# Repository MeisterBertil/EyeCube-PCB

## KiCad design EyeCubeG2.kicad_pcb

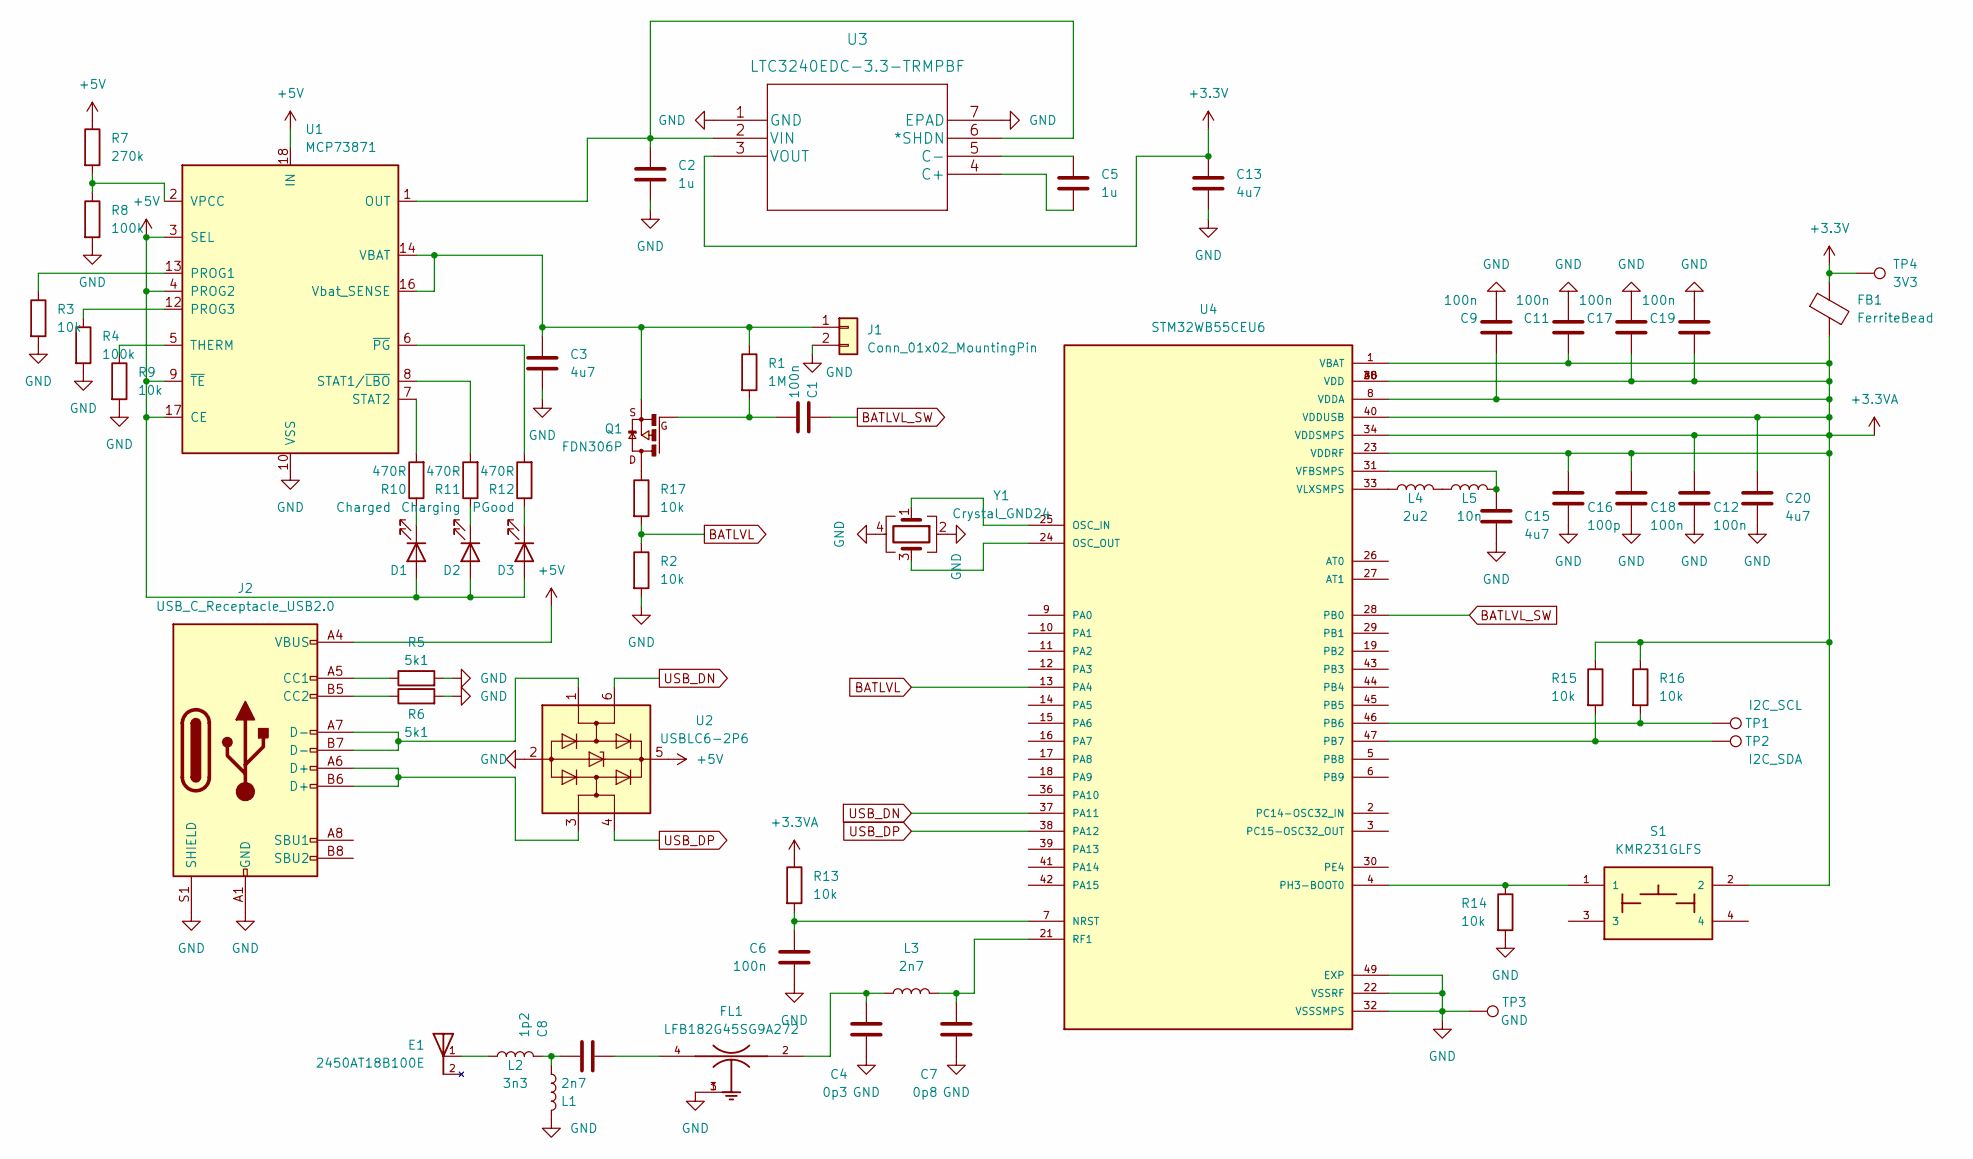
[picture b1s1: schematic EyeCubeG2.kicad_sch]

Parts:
C1, C6, C9, C11, C12, C17, C18, C19: 100n; C_0402_1005Metric
C2, C5: 1u; C_0402_1005Metric
C3, C13, C15, C20: 4u7; C_0603_1608Metric
C4: 0p3; C_0402_1005Metric
C7: 0p8; C_0402_1005Metric
C8: 1p2; C_0402_1005Metric
C16: 100p; C_0402_1005Metric
D1: Charged; D_0402_1005Metric
D2: Charging; D_0402_1005Metric
D3: PGood; D_0402_1005Metric
E1: 2450AT18B100E; XDCR_2450AT18B100E; PARTREV 4.0
FB1: FerriteBead; L_0402_1005Metric
FL1: LFB182G45SG9A272; FIL_LFB182G45SG9A272; PARTREV N/A
J1: Conn_01x02_MountingPin; JST_PH_S2B-PH-K_1x02_P2.00mm_Horizontal
J2: USB_C_Receptacle_USB2.0; USB_C_Receptacle_HRO_TYPE-C-31-M-12
L1, L3: 2n7; L_0402_1005Metric
L2: 3n3; L_0402_1005Metric
L4: 2u2; L_0402_1005Metric
L5: 10n; L_0402_1005Metric
Q1: FDN306P; SSOT-3
R1: 1M; R_0402_1005Metric
R2, R3, R9, R13, R14, R15, R16, R17: 10k; R_0402_1005Metric
R4, R8: 100k; R_0402_1005Metric
R5, R6: 5k1; R_0402_1005Metric
R7: 270k; R_0402_1005Metric
R10, R11, R12: 470R; R_0402_1005Metric
S1: KMR231GLFS; SW4SMD_63X161LS
TP1: I2C_SCL; TestPoint_Pad_D4.0mm
TP2: I2C_SDA; TestPoint_Pad_D4.0mm
TP3: GND; TestPoint_Pad_D4.0mm
TP4: 3V3; TestPoint_Pad_D4.0mm
U1: MCP73871; QFN-20-1EP_4x4mm_P0.5mm_EP2.5x2.5mm
U2: USBLC6-2P6; SOT-666
U3: LTC3240EDC-3.3-TRMPBF; DFN-6-1EP_2x2mm_P0.5mm_EP0.61x1.42mm
U4: STM32WB55CEU6; QFN50P700X700X60-49N; PARTREV 5
Y1: Crystal_GND24; Crystal_SMD_2016-4Pin_2.0x1.6mm

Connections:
+3.3VA: C9.1, C11.1, C12.1, C16.1, C17.1, C18.1, C19.1, C20.1, FB1.2, R13.1, R15.1, R16.1, S1.2, U4.1 (VBAT), U4.8 (VDDA), U4.20 (VDD), U4.23 (VDDRF), U4.34 (VDDSMPS), U4.35 (VDD), U4.40 (VDDUSB), U4.48 (VDD)
+3V3: C13.1, FB1.1, TP4.1, U3.3 (VOUT)
+5V: D1.2 (A), D2.2 (A), D3.2 (A), J2.A4 (VBUS), J2.A9 (VBUS), J2.B4 (VBUS), J2.B9 (VBUS), R7.1, U1.3 (SEL), U1.4 (PROG2), U1.9 (~TE), U1.17 (CE), U1.18 (IN), U1.19 (IN), U2.5 (VBUS)
BATLVL: R2.1, R17.2, U4.13 (PA4)
BATLVL_SW: C1.2, U4.28 (PB0)
GND: C2.2, C3.2, C4.2, C6.2, C7.2, C9.2, C11.2, C12.2, C13.2, C15.2, C16.2, C17.2, C18.2, C19.2, C20.2, FL1.1, FL1.3, J1.2, J2.A1 (GND), J2.A12 (GND), J2.B1 (GND), J2.B12 (GND), J2.S1 (SHIELD), L1.1, R2.2, R3.2, R4.2, R5.2, R6.2, R8.2, R9.2, R14.2, TP3.1, U1.10 (VSS), U1.11 (VSS), U1.21 (VSS), U2.2 (GND), U3.1 (GND), U3.7 (EPAD), U4.22 (VSSRF), U4.32 (VSSSMPS), U4.49 (EXP), Y1.2, Y1.4
unnamed: C1.1, Q1.1, R1.2
unnamed: C2.1, U1.1 (OUT), U1.20 (OUT), U3.2 (VIN), U3.6 (*SHDN)
unnamed: C3.1, J1.1, Q1.2, R1.1, U1.14 (VBAT), U1.15 (VBAT), U1.16 (Vbat_SENSE)
unnamed: C4.1, FL1.2, L3.2
unnamed: C5.1, U3.5 (C-)
unnamed: C5.2, U3.4 (C+)
unnamed: C6.1, R13.2, U4.7 (NRST)
unnamed: C7.1, L3.1, U4.21 (RF1)
unnamed: C8.1, FL1.4
unnamed: C8.2, L1.2, L2.2
unnamed: C15.1, L5.1, U4.31 (VFBSMPS)
unnamed: D1.1 (K), R10.1
unnamed: D2.1 (K), R11.1
unnamed: D3.1 (K), R12.1
unnamed: E1.1, L2.1
unnamed: J2.A5 (CC1), R5.1
unnamed: J2.A6 (D+), J2.B6 (D+), U2.3 (I/O2)
unnamed: J2.A7 (D-), J2.B7 (D-), U2.1 (I/O1)
unnamed: J2.B5 (CC2), R6.1
unnamed: L4.1, L5.2
unnamed: L4.2, U4.33 (VLXSMPS)
unnamed: Q1.3, R17.1
unnamed: R3.1, U1.13 (PROG1)
unnamed: R4.1, U1.12 (PROG3)
unnamed: R7.2, R8.1, U1.2 (VPCC)
unnamed: R9.1, U1.5 (THERM)
unnamed: R10.2, U1.7 (STAT2)
unnamed: R11.2, U1.8 (STAT1/~LBO)
unnamed: R12.2, U1.6 (~PG)
unnamed: R14.1, S1.1, U4.4 (PH3-BOOT0)
unnamed: R15.2, TP2.1, U4.47 (PB7)
unnamed: R16.2, TP1.1, U4.46 (PB6)
unnamed: U4.24 (OSC_OUT), Y1.3
unnamed: U4.25 (OSC_IN), Y1.1
USB_DN: U2.6 (I/O1), U4.37 (PA11)
USB_DP: U2.4 (I/O2), U4.38 (PA12)

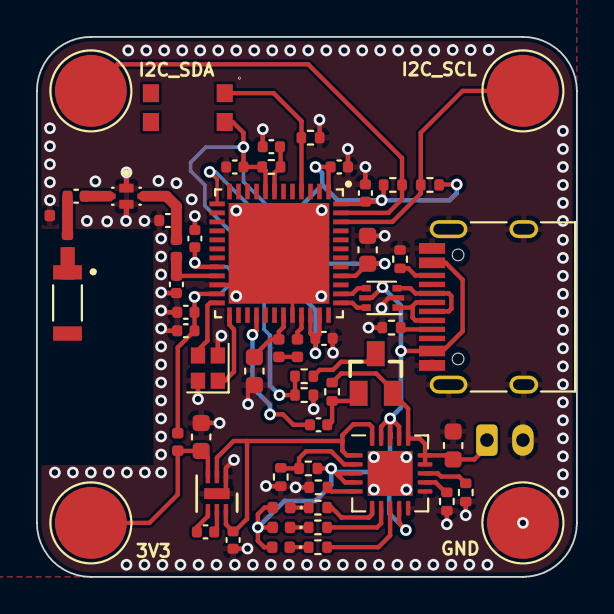
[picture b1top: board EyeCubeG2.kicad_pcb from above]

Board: 2 copper layers, 30.0 x 30.0 mm, 59 parts (1 on the bottom side), 42 nets.

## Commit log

2023-02-05 New step file
